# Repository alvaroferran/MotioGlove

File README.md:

MotioGlove
===================================================================

<br;>
<br;>
MotioGlove is an inertial remote controller. The board mounts an Atmega328P working at 8Mhz and 3.3V, a BC-04 bluetooth module, a [BNO055 IMU](https://github.com/bqlabs/BNO055) and a 1-cell Lipo Charger. The USB to UART converter is a CH340, so its driver must be downloaded.

It has been used as a controller for [Loki](https://github.com/bqlabs/loki/tree/develop/loki), an omnidirectional robot, among others. Don't hesitate to contribute with your examples!

Attributions
--------------------------------------------------------------
 - [Alvaro Ferrán Cifuentes](https://github.com/alvaroferran)
  - HW & SW design

- [Sonia Verdú ](https://github.com/soniaverdu)
  - Mechanical design

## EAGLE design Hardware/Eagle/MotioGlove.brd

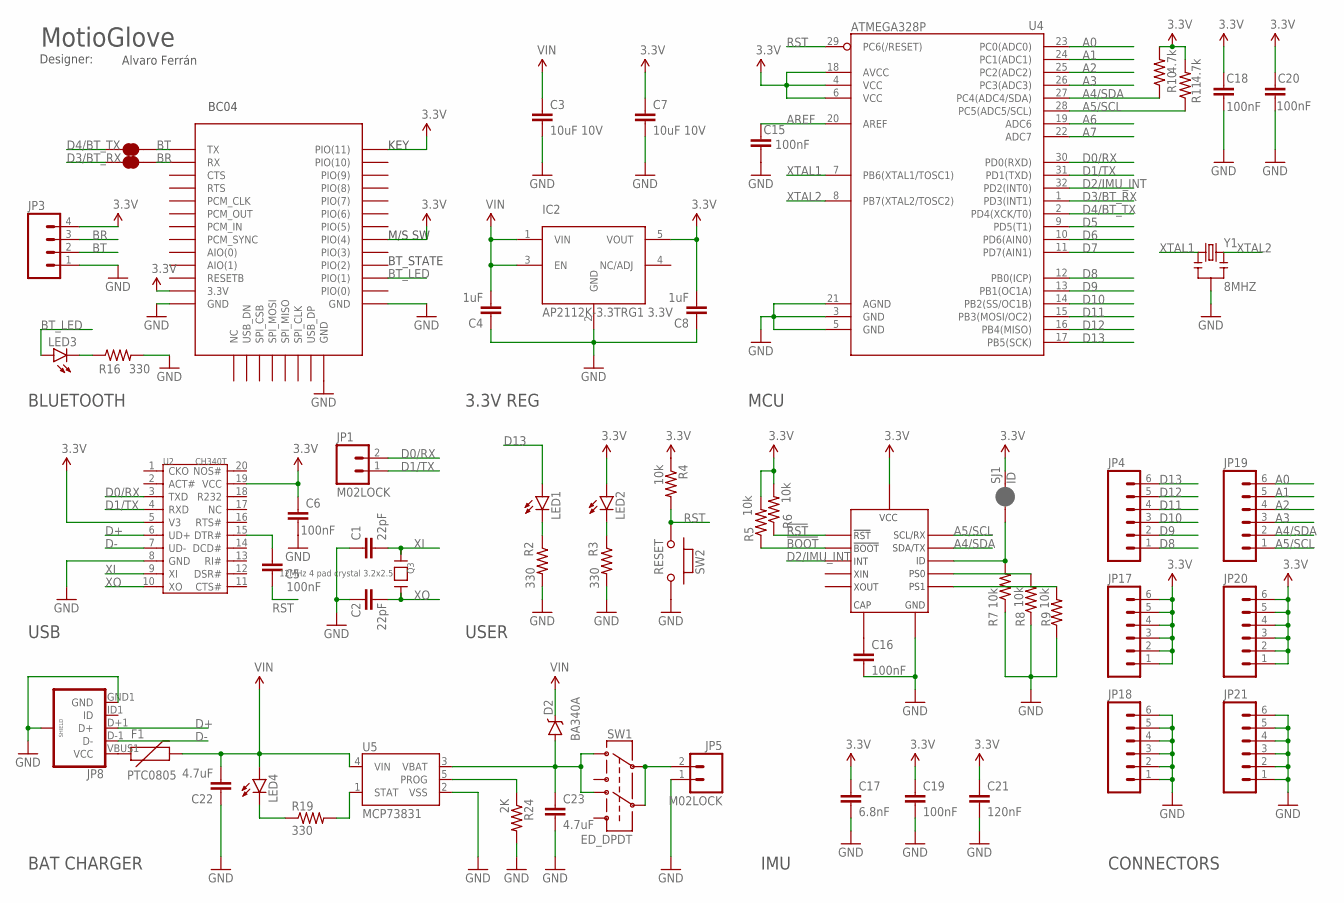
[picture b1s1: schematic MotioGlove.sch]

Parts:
C1, C2: 22pF; 0402-CAP
C3, C7: 10uF 10V; 0603-CAP
C4, C8: 1uF; 0603-CAP
C5, C6, C15, C18, C20: 100nF; 0402-CAP
C16, C19: 100nF; 0603-CAP
C17: 6.8nF; 0603-CAP
C21: 120nF; 0603-CAP
C22, C23: 4.7uF; 0402-CAP
D2: BA340A; SMA-DIODE
F1: PTC0805; 0805
IC2: AP2112K-3.3TRG1 3.3V; SOT23-5
IC3: BC04_BLUETOOTH; BC04
JP1, JP5: M02LOCK; 1X02_LOCK
JP3: M04LOCK; 1X04_LOCK
JP4, JP17, JP18, JP19, JP20, JP21: M06LOCK; 1X06_LOCK
JP8: USB_MICROB_PLUGCONN-11752; USB-B-MICRO-SMD_V03
LED1, LED2, LED3, LED4: LED0603; LED-0603
Q3: 12MHz 4 pad crystal 3.2x2.5; CRYSTAL_3.2X2.5
R: JUMPER-PAD-2-NC_BY_TRACE; PAD-JUMPER-2-NC_BY_TRACE_YES_SILK
R2, R3, R16, R19: 330; 0402-RES
R4, R5, R6, R7, R8, R9: 10k; 0402-RES
R10, R11: 4.7k; 0402-RES
R24: 2K; 0402-RES
SJ1: ID; PAD-JUMPER-2-NC_BY_PASTE_YES_SILK
SW1: ED_DPDT
SW2: RESET; 157SW
T: JUMPER-PAD-2-NC_BY_TRACE; PAD-JUMPER-2-NC_BY_TRACE_YES_SILK
U2: CH340T; SSOP20
U3: BNO055
U4: ATMEGA328P; TQFP32-08
U5: MCP73831; SOT23-5
Y1: 8MHZ; RESONATOR-SMD

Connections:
3.3V: C6.1, C7.1, C8.2, C17.1, C18.1, C19.1, C20.1, C21.1, IC2.5 (VOUT), IC3.P$12 (3.3V), IC3.P$27 (PIO(4)), IC3.P$34 (PIO(11)), JP3.4, JP17.1, JP17.2, JP17.3, JP17.4, JP17.5, JP17.6, JP20.1, JP20.2, JP20.3, JP20.4, JP20.5, JP20.6, LED2.A, R4.1, R5.2, R6.2, R10.2, R11.2, SJ1.2, U2.5 (V3), U2.19 (VCC), U3.3 (VCC), U3.28 (VCC), U4.4 (VCC), U4.6 (VCC), U4.18 (AVCC)
!BOOT: R5.1, U3.4 (BOOT)
!RST: R6.1, U3.11 (RST)
A0: JP19.6, U4.23 (PC0(ADC0))
A1: JP19.5, U4.24 (PC1(ADC1))
A2: JP19.4, U4.25 (PC2(ADC2))
A3: JP19.3, U4.26 (PC3(ADC3))
A4/SDA: JP19.2, R10.1, U3.20 (SDA/TX), U4.27 (PC4(ADC4/SDA))
A5/SCL: JP19.1, R11.1, U3.19 (SCL/RX), U4.28 (PC5(ADC5/SCL))
A6: U4.19 (ADC6)
A7: U4.22 (ADC7)
AREF: C15.1, U4.20 (AREF)
BR: IC3.P$2 (RX), JP3.3, R.2
BT: IC3.P$1 (TX), JP3.2, T.2
BT_LED: IC3.P$24 (PIO(1)), LED3.A
D0/RX: JP1.2, U2.3 (TXD), U4.30 (PD0(RXD))
D1/TX: JP1.1, U2.4 (RXD), U4.31 (PD1(TXD))
D2/IMU_INT: U3.14 (INT), U4.32 (PD2(INT0))
D3/BT_RX: R.1, U4.1 (PD3(INT1))
D4/BT_TX: T.1, U4.2 (PD4(XCK/T0))
D5: U4.9 (PD5(T1))
D6: U4.10 (PD6(AIN0))
D7: U4.11 (PD7(AIN1))
D8: JP4.1, U4.12 (PB0(ICP))
D9: JP4.2, U4.13 (PB1(OC1A))
D10: JP4.3, U4.14 (PB2(SS/OC1B))
D11: JP4.4, U4.15 (PB3(MOSI/OC2))
D12: JP4.5, U4.16 (PB4(MISO))
D13: JP4.6, LED1.A, U4.17 (PB5(SCK))
D+: JP8.D+1 (D+), U2.6 (UD+)
D-: JP8.D-1 (D-), U2.7 (UD-)
GND: C1.1, C2.1, C3.2, C4.1, C6.2, C7.2, C8.1, C15.2, C16.2, C17.2, C18.2, C19.2, C20.2, C21.2, C22.1, C23.2, IC2.2 (GND), IC3.P$13 (GND), IC3.P$21 (GND), IC3.P$22 (GND), JP3.1, JP5.1, JP8.GND1 (GND), JP8.SHIELD1 (SHIELD), JP8.SHIELD2 (SHIELD), JP8.SHIELD3 (SHIELD), JP18.1, JP18.2, JP18.3, JP18.4, JP18.5, JP18.6, JP21.1, JP21.2, JP21.3, JP21.4, JP21.5, JP21.6, R2.2, R3.2, R7.1, R8.1, R9.1, R16.2, R24.2, SW2.2, U2.8 (GND), U3.2 (GND), U3.10 (GND), U3.15 (GND), U3.16 (GND), U3.18 (GND), U3.25 (GND), U4.3 (GND), U4.5 (GND), U4.21 (AGND), U5.2 (VSS), Y1.2
unnamed: C5.1, U2.15 (DTR#)
unnamed: R7.2, SJ1.1, U3.17 (ID)
unnamed: JP5.2, SW1.2, SW1.5
unnamed: F1.1, JP8.VBUS1 (VCC)
unnamed: R8.2, U3.6 (PS0)
unnamed: R9.2, U3.5 (PS1)
unnamed: LED1.C, R2.1
unnamed: C16.1, U3.9 (CAP)
unnamed: R19.2, U5.1 (STAT)
unnamed: LED3.C, R16.1
unnamed: LED4.C, R19.1
unnamed: LED2.C, R3.1
PROG: R24.1, U5.5 (PROG)
RST: C5.2, R4.2, SW2.1, U4.29 (PC6(/RESET))
VBAT: C23.1, D2.A, SW1.1, SW1.4, U5.3 (VBAT)
VIN: C3.1, C4.2, C22.2, D2.C, F1.2, IC2.1 (VIN), IC2.3 (EN), LED4.A, U5.4 (VIN)
XI: C1.2, Q3.3, U2.9 (XI)
XO: C2.2, Q3.1, U2.10 (XO)
XTAL1: U4.7 (PB6(XTAL1/TOSC1)), Y1.1
XTAL2: U4.8 (PB7(XTAL2/TOSC2)), Y1.3

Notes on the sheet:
3.3V REG
USB
MCU
IMU
MotioGlove
Designer:
Alvaro Ferrán
USER
BAT CHARGER
BLUETOOTH
BC04
KEY
M/S SW
BT_STATE
CONNECTORS

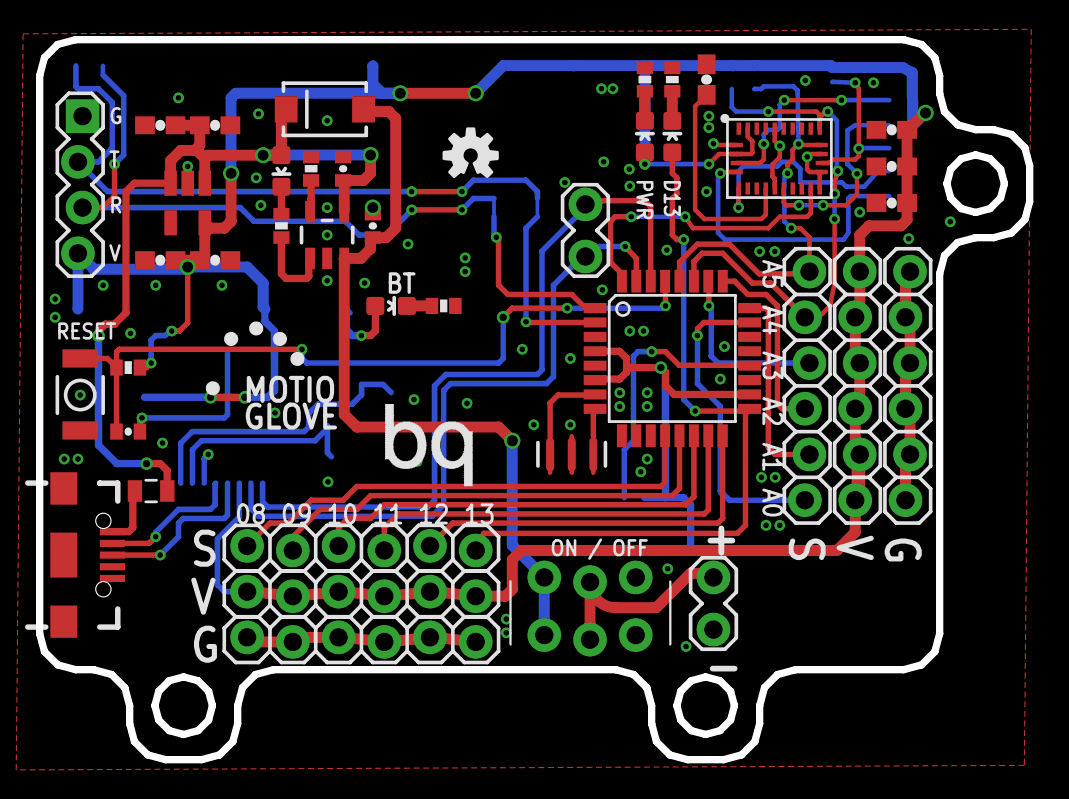
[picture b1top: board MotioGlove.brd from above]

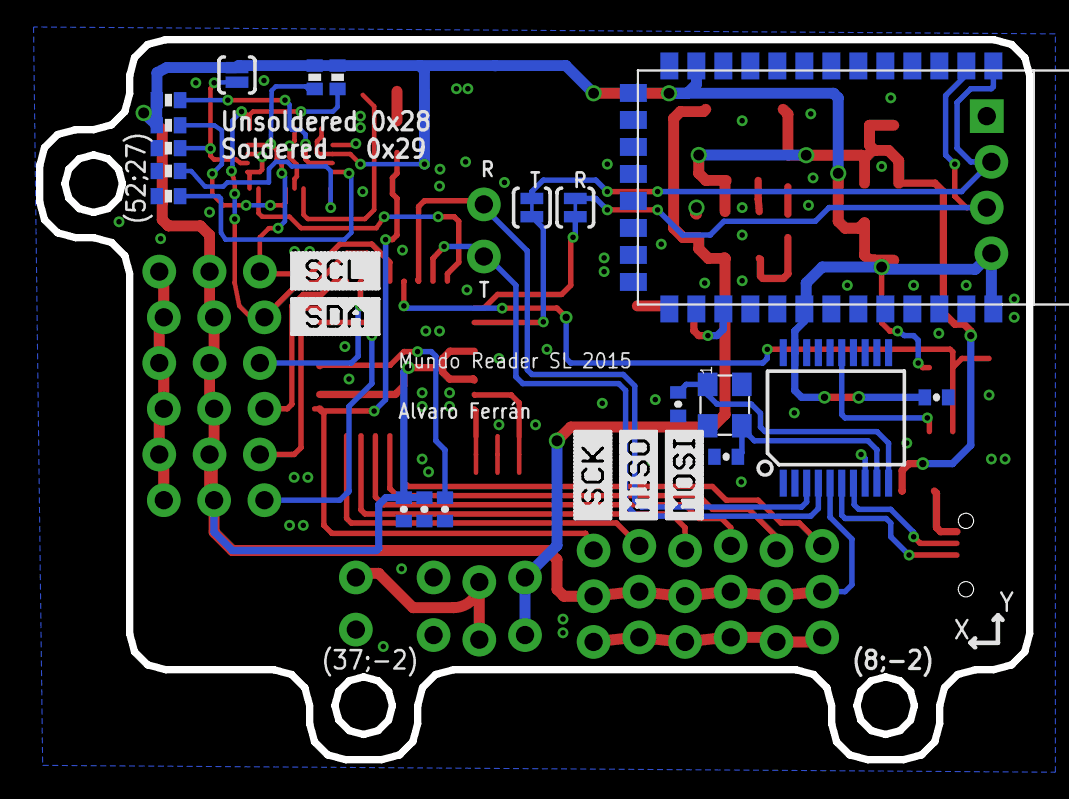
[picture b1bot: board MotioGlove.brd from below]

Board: 2 copper layers, 55.0 x 40.0 mm, 67 parts (24 on the bottom side), 47 nets.

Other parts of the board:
U$1: BQ_LOGO_1
U$2: S_SDA
U$3: OSHW-LOGO-S
U$4: BQ_LOGO_SMALL_2
U$5: S_SCL
U$6: S_MOSI
U$7: S_MISO
U$8: S_SCK

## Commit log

2015-12-03 Project added
2016-03-14 json added
2016-06-15 refactored code
2018-10-20 Update license to GPLv3

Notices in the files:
parts and their libraries:
SparkFun-Passives: Licensing: Creative Commons ShareAlike 4.0 International - https://creativecommons.org/licenses/by-sa/4.0
